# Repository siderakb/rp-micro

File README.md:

# RP Micro

*RP Micro* is a Pro Micro compatible RP2040 board with USB Type-C and 8MB flash, inspired by the [plut0nium/0xB2](https://github.com/plut0nium/0xB2), [joshajohnson/sea-picro](https://github.com/joshajohnson/sea-picro) and [Elite-Pi](https://docs.keeb.io/elite-pi-guide), specialized design for keyboards.

Go to [Releases](https://github.com/siderakb/rp-micro/releases) for Gerber, schematic and PCBA files.

> A part of [ErgoSNM keyboard](https://github.com/siderakb/ergo-snm-keyboard) project.

## Pinout

- [SparkFun Pro Micro - RP2040](https://www.sparkfun.com/products/18288) compatible pinout, with additional 5+2 pins (Elite-C and Elite-Pi style, but the pinout not identical to Elite-Pi).
- RAW: LDO regulator VIN pin.
- Blue LED `LD1`: State/User LED (Connect to GP25).
- All the GPIO pins of RP2040 can be used as PWM output.
- Select whether the 3rd and 4th pads in the left column are GND or GP10/GP11 by using solder bridge jumper `SB1` and `SB2`, the default is GND. To access GP10 or GP11, you need to cut the track between the solder bridge and GND pad, and then connect to the GPIO pads with solder. Great idea from Elite-Pi.

The RP2040 GPIO pin functions is very flexible, the above pinout figure is a simplified version, please refer to the [RP2040 datasheet](https://datasheets.raspberrypi.com/rp2040/rp2040-datasheet.pdf) "*1.4.3. GPIO Functions*" section for details.

## BOM
| Designator                        | Value                          | Footprint                           | Description                                       |
| --------------------------------- | ------------------------------ | ----------------------------------- | ------------------------------------------------- |
| R1,R2                             | 27                             | 0402 (1005 Metric)                  | RP2040 USB D+/- series termination resistors      |
| R3,R4,R9                          | 1k                             | 0402 (1005 Metric)                  |                                                   |
| R5,R8                             | 10k                            | 0402 (1005 Metric)                  |                                                   |
| R6,R7                             | 5.1k                           | 0402 (1005 Metric)                  | USB Type-C CC resistors                           |
| C1,C2,C5,C6,C8,C9,C10,C11,C12,C15 | 100nF                          | 0402 (1005 Metric)                  | Flash and RP2040 decoupling capacitors            |
| C3,C4                             | 20pF                           | 0402 (1005 Metric)                  | Crystal load capacitors                           |
| C7,C13,C14,C16                    | 1uF                            | 0402 (1005 Metric)                  | LDO input/output and RP2040 decoupling capacitors |
| LD1                               | BLUE                           | 0603 (1608 Metric)                  | State/User LED                                    |
| D1                                | B5817                          | SOD-323                             | USB VBUS diode                                    |
| F1                                | 500mA, 6V                      | 0805 (2012 Metric)                  | USB VBUS fuse                                     |
| J1                                | USB-C Mid-Mount Receptacle 16P | 918-418K2024S40000                  | USB Type-C connector                              |
| SW1,SW2                           | BOOT and RESET buttons         | B3U-1000P                           | Buttons                                           |
| U1                                | RP2040                         | QFN-56-1EP 7x7mm P0.4mm EP3.2x3.2mm | MCU                                               |
| U2                                | W25Q64JVXGIQ                   | XSON-8 (4x4mm)                      | 8MB (64Mbit) flash                                |
| U3                                | RT9013-33GB                    | SOT-23-5                            | 3.3V/500mA LDO regulator                          |
| Y1                                | 12MHz                          | 3225-4Pin (3.2x2.5mm)               | Crystal for RP2040                                |

There is not designator silkscreen on PCB, please use your browser to open the `ibom.html` file (placed in [Release page](https://github.com/siderakb/rp-micro/releases) and [`bom/ibom.html`](./bom/ibom.html)) to refer to the placement of the parts, it is generated by [Interactive HTML BOM](https://github.com/openscopeproject/InteractiveHtmlBom) plugin. 

> See also [`PCBA/rp-micro_bom.csv`](./PCBA/rp-micro_bom.csv)

## PCB

|                   Top                   |                   Bottom                   |                   Layers                   |
| :-------------------------------------: | :----------------------------------------: | :----------------------------------------: |
|  |  |  |

## PCBA

Support JLCPCB's PCBA service, the BOM and CPL files for PCBA are placed in the [`PCBA`](./PCBA/) folder and [Releases](https://github.com/ziteh/rp-micro/releases) page, files are generated by [KiCad JLCPCB Tools](https://github.com/Bouni/kicad-jlcpcb-tools) plugin.

## Board Characteristics

- Copper layer count: 2
- Board thickness: 1.6 mm
- Board overall dimensions: 17.78 x 33.02 mm (0.7 x 1.3 inch)
- Min track/spacing: 0.127 mm / 0.127 mm
- Min hole diameter: 0.3 mm
- Castellated pads: No
- Edge card connectors: No
- Plated board edge: No

## Disclaimer

These files are provided **AS IS**, without warranty of any kind, express or implied.  
Including but not limited to manufacturing, assembly, procurement and use at your own risk.  
It is recommended to check yourself before use.

For the full statement, please see [LICENSE](./LICENSE).

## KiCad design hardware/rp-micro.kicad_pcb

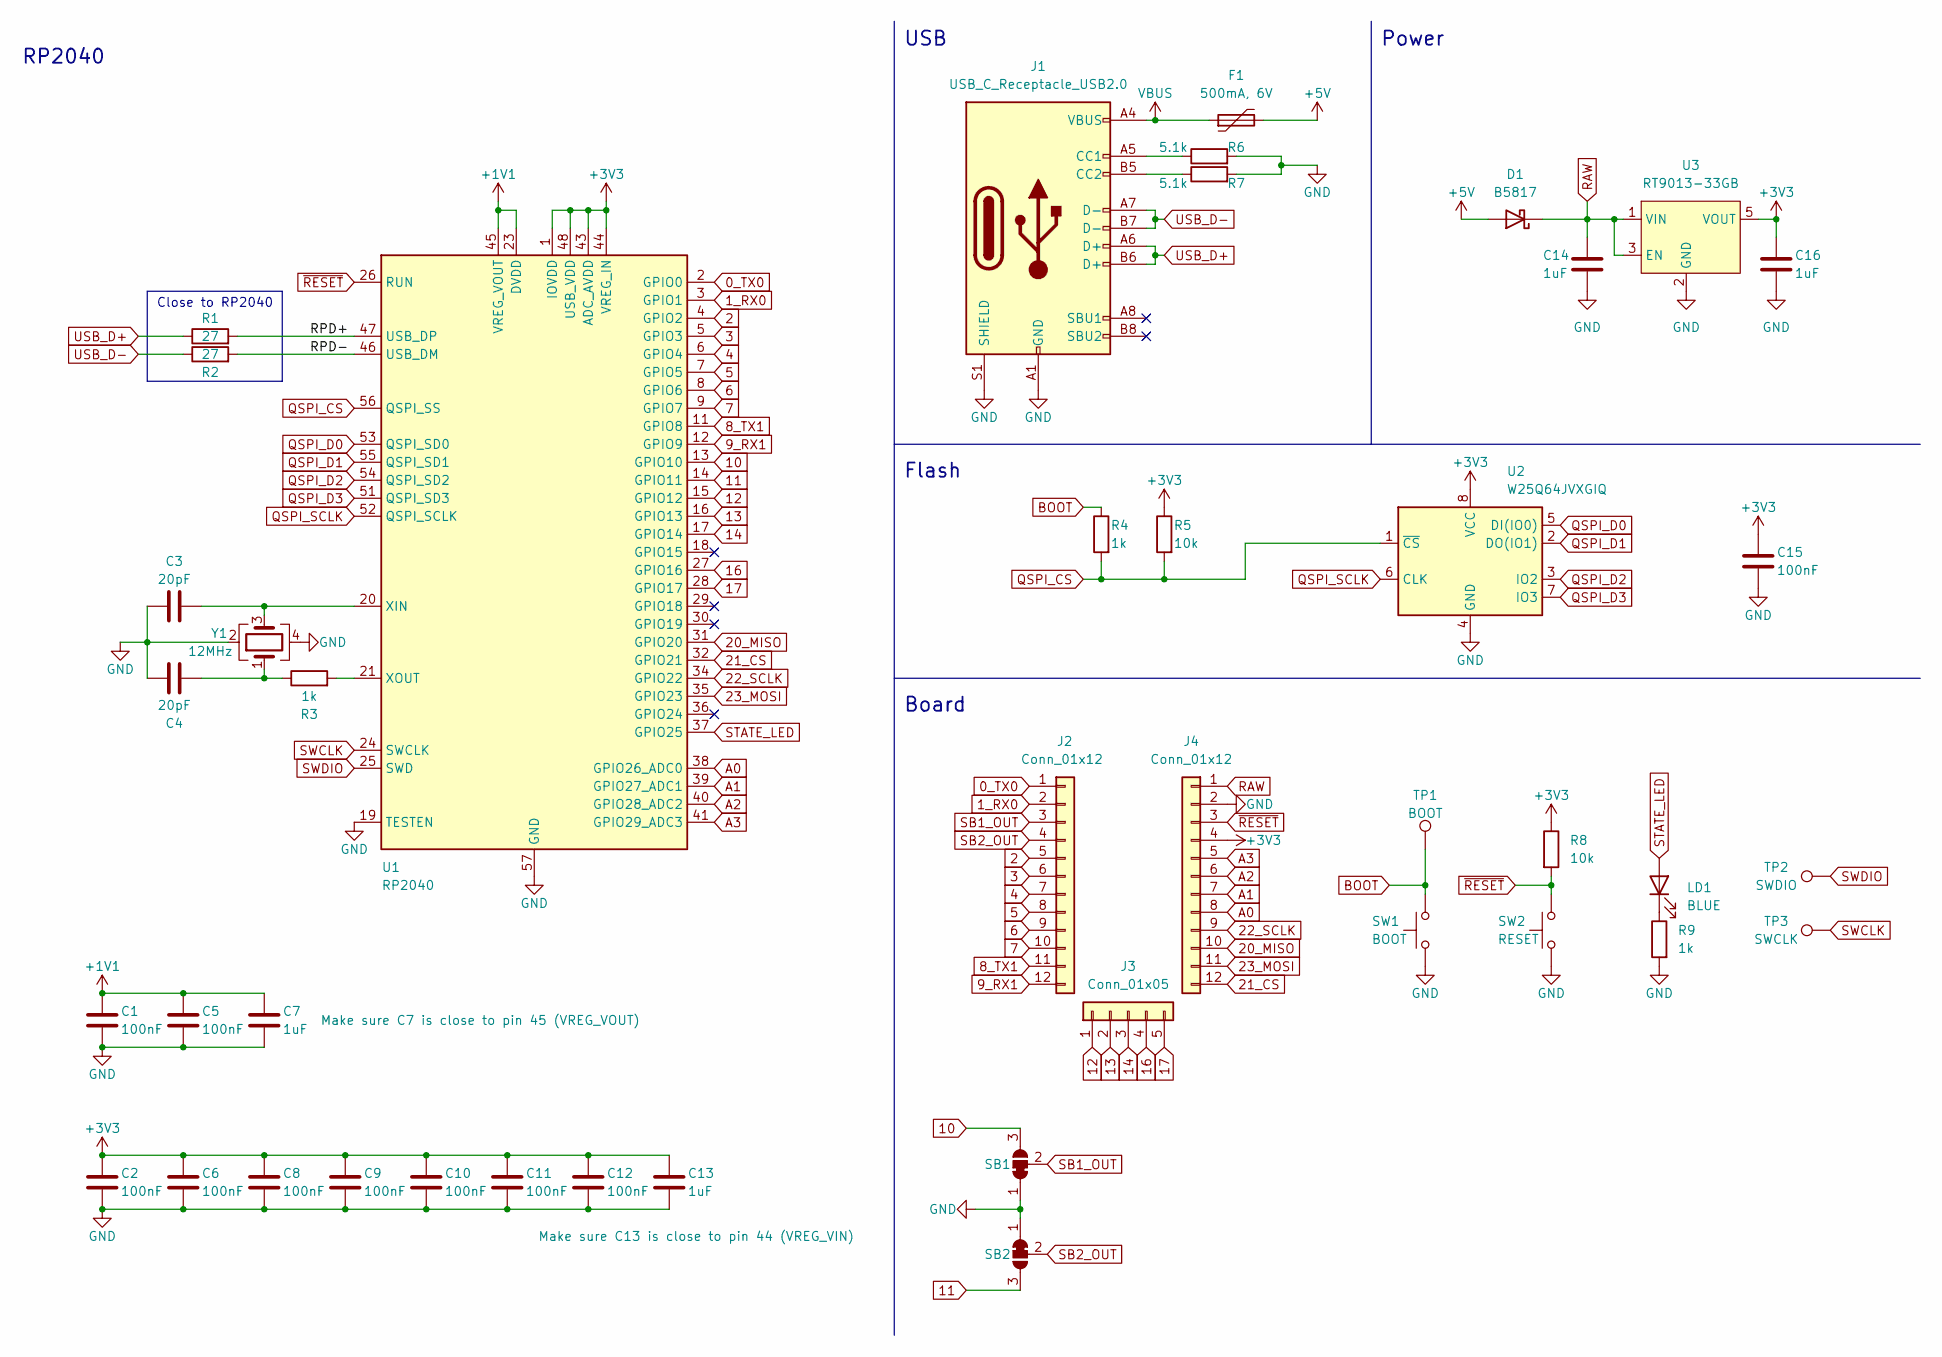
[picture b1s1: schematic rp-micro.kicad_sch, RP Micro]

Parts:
C1, C2, C5, C6, C8, C9, C10, C11, C12, C15: 100nF; C_0402_1005Metric; MFR. Part # CL05B104KB54PNC; JLCPCB Part # C307331
C3, C4: 20pF; C_0402_1005Metric; MFR. Part # 0402CG200J500NT; JLCPCB Part # C1554
C7, C13, C14, C16: 1uF; C_0402_1005Metric; MFR. Part # CL05A105KA5NQNC; JLCPCB Part # C52923
D1: B5817; D_SOD-323_HandSoldering; MFR. Part # B5817WS; JLCPCB Part # C123899
F1: 500mA, 6V; Fuse_0805_2012Metric; MFR. Part # SMD0805B050TF; JLCPCB Part # C269104
J1: USB_C_Receptacle_USB2.0; USB Type-C Mid-Mount Receptacle 16P; MFR. Part # 918-418K2024S40000; JLCPCB Part # C168688
J2, J4: Conn_01x12; PinHeader_1x12_P2.54mm_Vertical
J3: Conn_01x05; PinHeader_1x05_P2.54mm_Vertical
LD1: BLUE; LED_0603_1608Metric; MFR. Part # 19-217/BHC-ZL1M2RY/3T; JLCPCB Part # C72041
R1, R2: 27; R_0402_1005Metric; MFR. Part # 0402WGF270JTCE; JLCPCB Part # C25100
R3, R4, R9: 1k; R_0402_1005Metric; MFR. Part # 0402WGF1001TCE; JLCPCB Part # C11702
R5, R8: 10k; R_0402_1005Metric; MFR. Part # 0402WGF1002TCE; JLCPCB Part # C25744
R6, R7: 5.1k; R_0402_1005Metric; MFR. Part # 0402WGF5101TCE; JLCPCB Part # C25905
SB1, SB2: SolderJumper_3_Bridged12; SolderJumper-3_P1.3mm_Bridged12_Pad1.0x1.5mm
SW1: BOOT; SW_SPST_B3U-1000P; MFR. Part # B3U-1000P; JLCPCB Part # C231329
SW2: RESET; SW_SPST_B3U-1000P; MFR. Part # B3U-1000P; JLCPCB Part # C231329
TP1: BOOT; TestPoint_Pad_D2.0mm
TP2: SWDIO; TestPoint_Pad_D2.0mm
TP3: SWCLK; TestPoint_Pad_D2.0mm
U1: RP2040; QFN-56-1EP_7x7mm_P0.4mm_EP3.2x3.2mm; MFR. Part # RP2040; JLCPCB Part # C2040
U2: W25Q64JVXGIQ; XSON-8 (4x4mm); MFR. Part # W25Q64JVXGIQ; JLCPCB Part # C2940195
U3: RT9013-33GB; SOT-23-5; MFR. Part # RT9013-33GB; JLCPCB Part # C47773
Y1: 12MHz; Crystal_SMD_3225-4Pin_3.2x2.5mm; MFR. Part # X322512MSB4SI; JLCPCB Part # C9002

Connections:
0_TX0: J2.1, U1.2 (GPIO0)
1_RX0: J2.2, U1.3 (GPIO1)
2: J2.5, U1.4 (GPIO2)
3: J2.6, U1.5 (GPIO3)
4: J2.7, U1.6 (GPIO4)
5: J2.8, U1.7 (GPIO5)
6: J2.9, U1.8 (GPIO6)
7: J2.10, U1.9 (GPIO7)
8_TX1: J2.11, U1.11 (GPIO8)
9_RX1: J2.12, U1.12 (GPIO9)
10: SB1.3 (B), U1.13 (GPIO10)
11: SB2.3 (B), U1.14 (GPIO11)
12: J3.1, U1.15 (GPIO12)
13: J3.2, U1.16 (GPIO13)
14: J3.3, U1.17 (GPIO14)
16: J3.4, U1.27 (GPIO16)
17: J3.5, U1.28 (GPIO17)
20_MISO: J4.10, U1.31 (GPIO20)
21_CS: J4.12, U1.32 (GPIO21)
22_SCLK: J4.9, U1.34 (GPIO22)
23_MOSI: J4.11, U1.35 (GPIO23)
+1V1: C1.1, C5.1, C7.1, U1.23 (DVDD), U1.45 (VREG_VOUT), U1.50 (DVDD)
+3V3: C2.1, C6.1, C8.1, C9.1, C10.1, C11.1, C12.1, C13.1, C15.1, C16.1, J4.4, R5.1, R8.1, U1.1 (IOVDD), U1.10 (IOVDD), U1.22 (IOVDD), U1.33 (IOVDD), U1.42 (IOVDD), U1.43 (ADC_AVDD), U1.44 (VREG_IN), U1.48 (USB_VDD), U1.49 (IOVDD), U2.8 (VCC), U3.5 (VOUT)
+5V: D1.2 (A), F1.2
/RPD+: R1.2, U1.47 (USB_DP)
/RPD-: R2.2, U1.46 (USB_DM)
A0: J4.8, U1.38 (GPIO26_ADC0)
A1: J4.7, U1.39 (GPIO27_ADC1)
A2: J4.6, U1.40 (GPIO28_ADC2)
A3: J4.5, U1.41 (GPIO29_ADC3)
BOOT: R4.1, SW1.2, TP1.1
GND: C1.2, C2.2, C3.1, C4.1, C5.2, C6.2, C7.2, C8.2, C9.2, C10.2, C11.2, C12.2, C13.2, C14.2, C15.2, C16.2, J1.A1 (GND), J1.A12 (GND), J1.B1 (GND), J1.B12 (GND), J1.S1 (SHIELD), J4.2, R6.2, R7.2, R9.2, SB1.1 (A), SB2.1 (A), SW1.1, SW2.1, U1.19 (TESTEN), U1.57 (GND), U2.4 (GND), U3.2 (GND), Y1.2, Y1.4
unnamed: C3.2, U1.20 (XIN), Y1.3
unnamed: C4.2, R3.1, Y1.1
unnamed: J1.A5 (CC1), R6.1
unnamed: J1.B5 (CC2), R7.1
unnamed: LD1.1 (K), R9.1
unnamed: R3.2, U1.21 (XOUT)
QSPI_CS: R4.2, R5.2, U1.56 (QSPI_SS), U2.1 (~CS)
QSPI_D0: U1.53 (QSPI_SD0), U2.5 (DI(IO0))
QSPI_D1: U1.55 (QSPI_SD1), U2.2 (DO(IO1))
QSPI_D2: U1.54 (QSPI_SD2), U2.3 (IO2)
QSPI_D3: U1.51 (QSPI_SD3), U2.7 (IO3)
QSPI_SCLK: U1.52 (QSPI_SCLK), U2.6 (CLK)
RAW: C14.1, D1.1 (K), J4.1, U3.1 (VIN), U3.3 (EN)
SB1_OUT: J2.3, SB1.2 (C)
SB2_OUT: J2.4, SB2.2 (C)
STATE_LED: LD1.2 (A), U1.37 (GPIO25)
SWCLK: TP3.1, U1.24 (SWCLK)
SWDIO: TP2.1, U1.25 (SWD)
USB_D+: J1.A6 (D+), J1.B6 (D+), R1.1
USB_D-: J1.A7 (D-), J1.B7 (D-), R2.1
VBUS: F1.1, J1.A4 (VBUS), J1.A9 (VBUS), J1.B4 (VBUS), J1.B9 (VBUS)
~RESET: J4.3, R8.2, SW2.2, U1.26 (RUN)

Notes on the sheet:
Flash
Close to RP2040
Power
RP2040
USB
Board

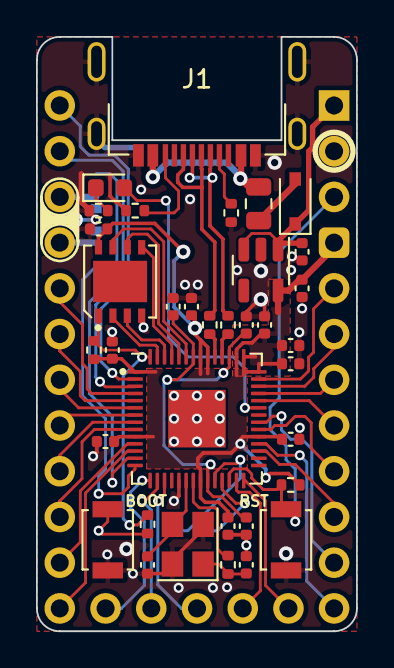
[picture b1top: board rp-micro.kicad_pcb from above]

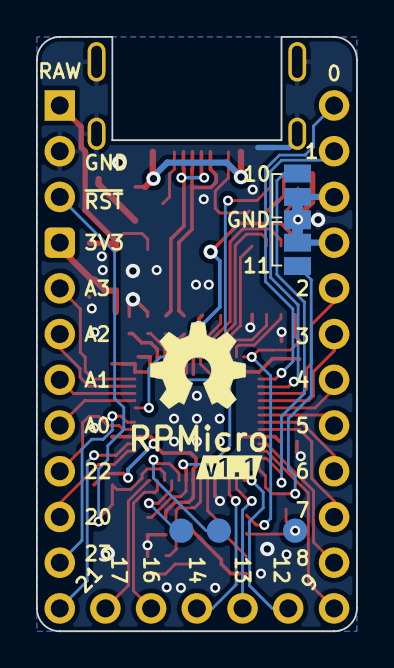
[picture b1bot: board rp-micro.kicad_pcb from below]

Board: 2 copper layers, 17.8 x 33.0 mm, 44 parts (8 on the bottom side), 54 nets.

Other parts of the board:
kibuzzard-637CA201: G***; kibuzzard-637CA201

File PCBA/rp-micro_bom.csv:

Comment,Designator,Footprint,LCSC
1k,"R3,R4,R9",R_0402_1005Metric,C11702
B5817,D1,D_SOD-323_HandSoldering,C123899
20pF,"C3,C4",C_0402_1005Metric,C1554
USB_C_Receptacle_USB2.0,J1,USB Type-C Mid-Mount Receptacle 16P,C168688
RP2040,U1,QFN-56-1EP_7x7mm_P0.4mm_EP3.2x3.2mm,C2040
BOOT,"SW1,SW2",SW_SPST_B3U-1000P,C231329
27,"R1,R2",R_0402_1005Metric,C25100
10k,"R5,R8",R_0402_1005Metric,C25744
5.1k,"R6,R7",R_0402_1005Metric,C25905
"500mA, 6V",F1,Fuse_0805_2012Metric,C269104
W25Q64JVXGIQ,U2,XSON-8 (4x4mm),C2940195
100nF,"C1,C10,C11,C12,C15,C2,C5,C6,C8,C9",C_0402_1005Metric,C307331
RT9013-33GB,U3,SOT-23-5,C47773
1uF,"C13,C14,C16,C7",C_0402_1005Metric,C52923
BLUE,LD1,LED_0603_1608Metric,C72041
12MHz,Y1,Crystal_SMD_3225-4Pin_3.2x2.5mm,C9002

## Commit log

2022-10-30 Add KiCad project
2022-11-01 Add BOM doc
2022-11-01 Add README.md
2022-11-01 Update license
2022-11-01 Move BOM
2022-11-01 Update track
2022-11-02 Update silkscreen
2022-11-03 Add PCBA files
2022-11-06 Rename BOM & CPL csv files
2022-11-06 Update BOM & CPL files for PCBA
2022-11-06 Update BOM
2022-11-07 Replace flash to W25Q64JVXGIQ
2022-11-07 Improve 3v3 route
2022-11-07 Update BOM and CPL files for PCBA
2022-11-07 Update note
2022-11-13 Fix the typo
2022-11-14 Update README.md
    Fix the typo
2022-11-22 rev 1.1 completed
2022-11-23 Update PCBA files
2022-11-23 Add `changelog.md`
2022-11-24 Update changelog
2022-12-07 Change D1 footprint to hand soldering version
2023-01-02 Update BOM, CPL , readme and changelog
2023-04-29 Add footprint and symbol library path table
2023-06-25 Update URL, replace "ziteh" with "siderakb".
2023-11-14 Change license from MIT to CERN-OHL-P v2
2024-05-28 Update issue templates
2024-07-08 Update README.md
    Fix typo
2025-04-17 chore: add `.gitattributes`

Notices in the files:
hardware/rp-micro.kicad_pcb:
Open source hardware, CERN-OHL-P v2
